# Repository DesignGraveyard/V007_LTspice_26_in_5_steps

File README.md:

# Description

In this step-by-step video tutorial, you will learn how to simulate electronic circuits in LTspice using a USB-powered audio amplifier as a practical example!  
We cover everything from drawing the schematic to importing third-party SPICE models & analyzing waveforms.   
At the end of the video we will build the amplifier and test the actual physical hardware on the bench. 

### Watch the YouTube video, it will guide you through the process step by step:  

Download LTspice Simulator:  
https://www.analog.com/en/resources/design-tools-and-calculators/ltspice-simulator.html

## Content in this GitHub repository:

### LTspice simulation files
The simulation file, schematic symbol and Spice model files.  
Unzip and double click the amplifier.asc file to open it in LTspice

### PCB Gerber files for the Amplifier
Send this zip file to your PCB manufacturer to directly order the Amplifier PCB's

### PCB_Material_BOM_Audio_amplifier
Material BOM to build the amplifier

### HTML_Signal_Generator
Single file offline signal generator used in this tutorial. (AI generated tool)  
Download "HTML_Signal_Generator.html" and open in your browser.  

### PCB_KiCAD_Files_Audio_amplifier
The PCB files made in KiCAD 10 in case you want to re-use or edit them.  
The folder also contains a pdf schematic and a 3D PCB render (png)

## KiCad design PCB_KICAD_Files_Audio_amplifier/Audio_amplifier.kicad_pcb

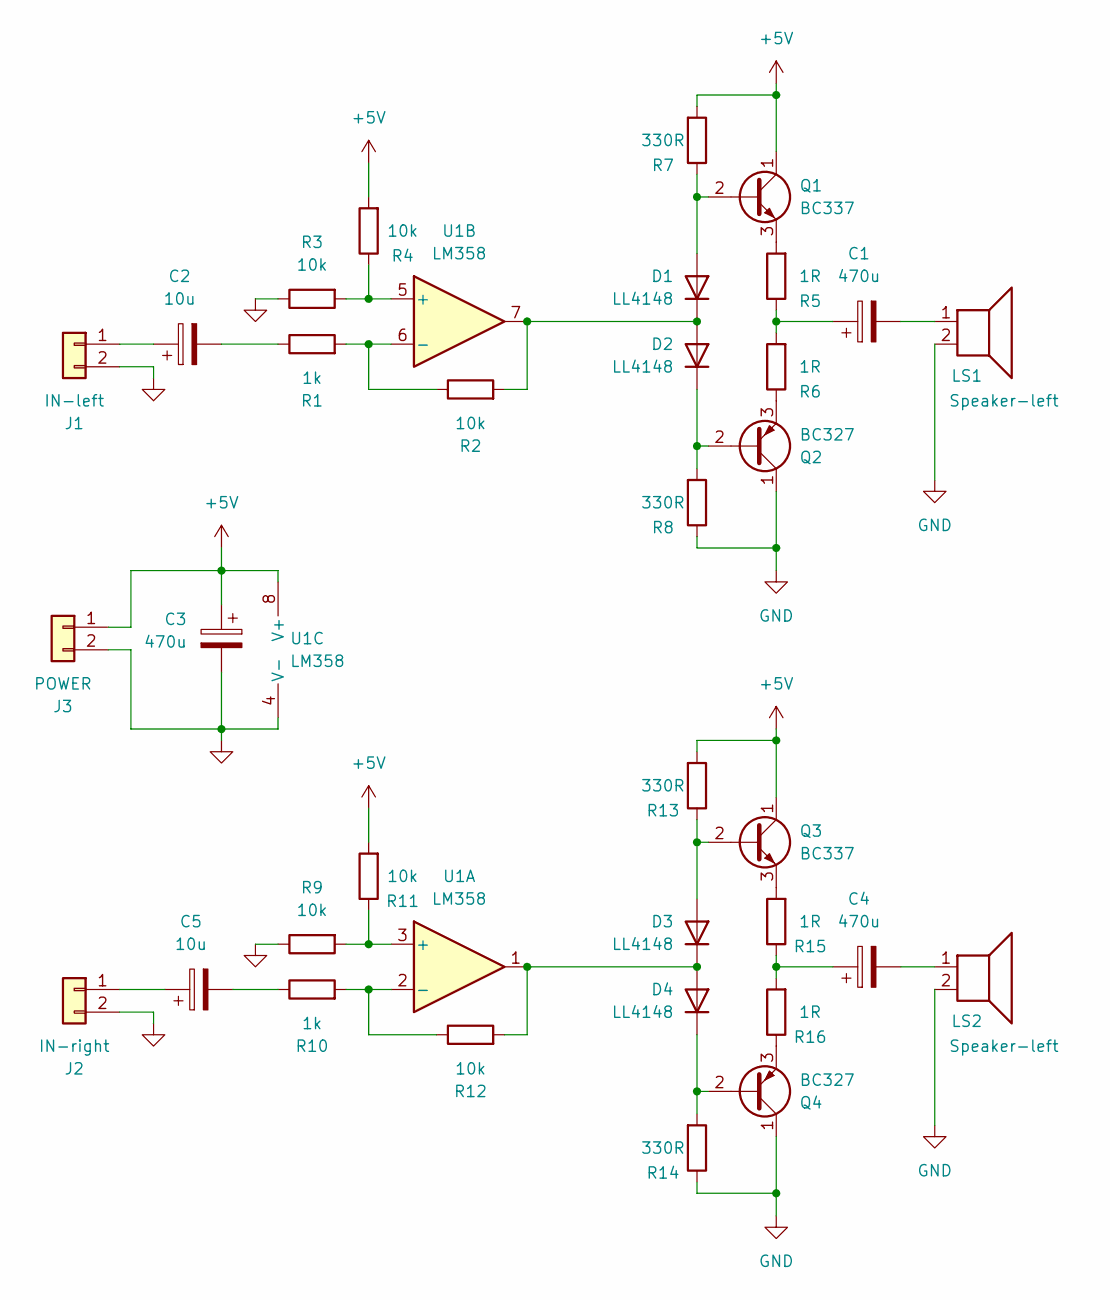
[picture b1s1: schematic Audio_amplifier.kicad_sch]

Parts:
C1, C3, C4: 470u; CP_Radial_D8.0mm_P3.80mm
C2, C5: 10u; CP_Radial_D5.0mm_P2.50mm
D1, D2, D3, D4: LL4148; D_MiniMELF
J1: IN-left; PinHeader_1x02_P2.54mm_Vertical
J2: IN-right; PinHeader_1x02_P2.54mm_Vertical
J3: POWER; PinHeader_1x02_P2.54mm_Vertical
LS1, LS2: Speaker-left; PinHeader_1x02_P2.54mm_Vertical
Q1, Q3: BC337; TO-92
Q2, Q4: BC327; TO-92
R1, R10: 1k; R_0805_2012Metric_Pad1.20x1.40mm_HandSolder
R2, R3, R4, R9, R11, R12: 10k; R_0805_2012Metric_Pad1.20x1.40mm_HandSolder
R5, R6, R15, R16: 1R; R_0805_2012Metric_Pad1.20x1.40mm_HandSolder
R7, R8, R13, R14: 330R; R_0805_2012Metric_Pad1.20x1.40mm_HandSolder
U1: LM358; DIP-8_W7.62mm

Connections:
+5V: C3.1, J3.1, Q1.1 (C), Q3.1 (C), R4.2, R7.2, R11.2, R13.2, U1.8 (V+)
GND: C3.2, J1.2, J2.2, J3.2, LS1.2, LS2.2, Q2.1 (C), Q4.1 (C), R3.1, R8.1, R9.1, R14.1, U1.4 (V-)
unnamed: C1.1, R5.1, R6.2
unnamed: C1.2, LS1.1
unnamed: C2.2, R1.1
unnamed: C4.1, R15.1, R16.2
unnamed: C4.2, LS2.1
unnamed: C5.2, R10.1
unnamed: D1.2 (A), Q1.2 (B), R7.1
unnamed: D1.1 (K), D2.2 (A), R2.2, U1.7
unnamed: D2.1 (K), Q2.2 (B), R8.2
unnamed: D3.2 (A), Q3.2 (B), R13.1
unnamed: D3.1 (K), D4.2 (A), R12.2, U1.1
unnamed: D4.1 (K), Q4.2 (B), R14.2
unnamed: C2.1, J1.1
unnamed: C5.1, J2.1
unnamed: Q1.3 (E), R5.2
unnamed: Q2.3 (E), R6.1
unnamed: Q3.3 (E), R15.2
unnamed: Q4.3 (E), R16.1
unnamed: R9.2, R11.1, U1.3 (+)
unnamed: R10.2, R12.1, U1.2 (-)
unnamed: R3.2, R4.1, U1.5 (+)
unnamed: R1.2, R2.1, U1.6 (-)

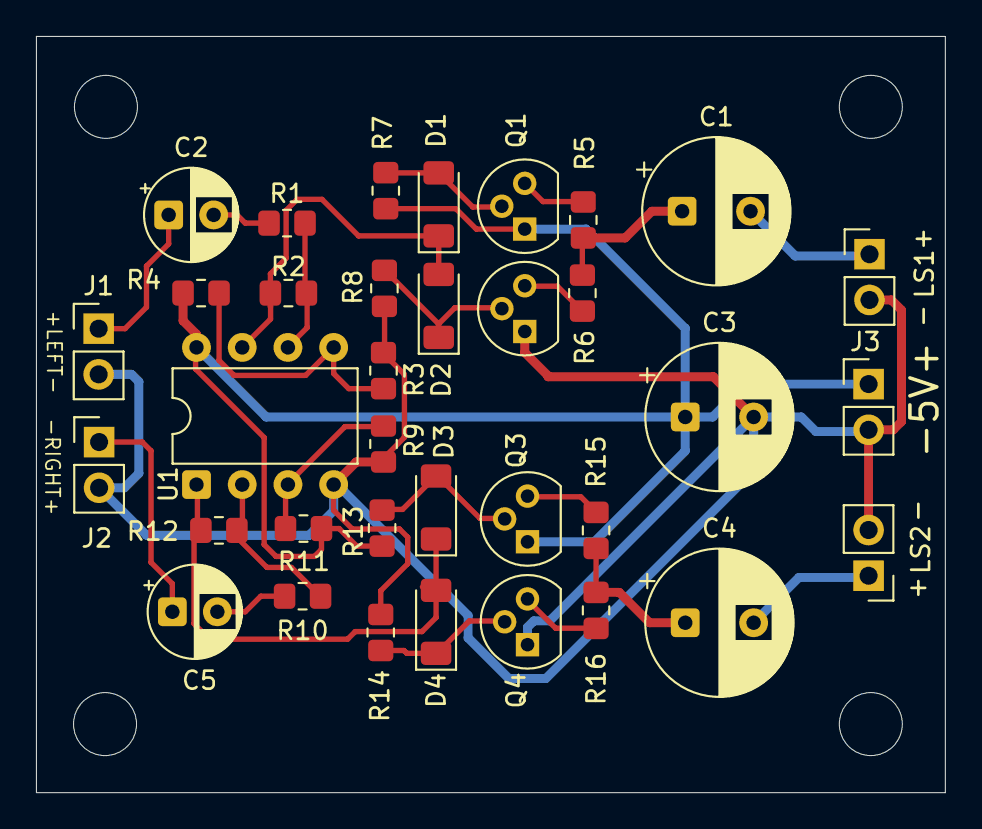
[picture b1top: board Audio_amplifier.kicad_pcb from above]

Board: 2 copper layers, 50.5 x 42.0 mm, 35 parts (0 on the bottom side), 24 nets.
